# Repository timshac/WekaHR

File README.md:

# WekaHR modbus slave holding registers synchronised with google sheets

The WekaHR is a modbus slave (RS-485) with read/write registers that are synced with your google sheet. Your PLC can connect to the WekaHR modbus slave to read and write register values to report data or configure PLC operations.

## Components

* WekaHR featherwing
* a PLC (supplied by you)
* Particle Argon (Wifi) or Boron (cellular) IOT device
* Google Sheet Application

## Connect hardware

1. Wire the WekaHR to your PLC.  The WekaHR is powered by 5v DC. Schnieder PLCs provide 5v via the modbus port
2. Insert the Boron or Argon into the WekaHR
3. Connnect particle Boron or Argon to the particle cloud, and give the device a name (deviceName)

Then you are ready to flash the firmware

## Flash Firmware

Clone this repository, and install the [particle command line tools](https://docs.particle.io/tutorials/developer-tools/cli/)

```
cd WekaHR/firmware/particle_gen3
# compile and flash over WiFi or Cellular
particle flash deviceName 

# or, for usb connected particle
particle compile argon|boron --saveTo=bin
particle serial list
particle serial flash bin
```

## Initial WekaHR module setup, for a fresh new module

Issue these commands to in the particle console (console.particle.io). The modbus baud is set in the code, currently to 19200 8N1
```
SetUnitID 10   # to set modbus slave ID (defaults to 10)
SetEventName "companyname/projectname"   # set the particle webhook event name

```

## Save a copy of the linked google sheet

Save a copy of this [WekaHR Google Sheets Template](https://docs.google.com/spreadsheets/d/1dsoAosavrSCt88q0tjWTA6WfT7lwxBgexuUGqGGjWAQ/copy?usp=sharing) and follow the instructions in the worksheet to connect your particle to the google sheet using a webhook.

## Connect particle cloud to google sheet

Follow the instructions in the google sheet to connect your particle device to the google sheeet using a particle webhook integration.

## Particle API - Functions

#### int ManualUpdate(String args = "")

Trigger a manual JSON packet publish and JSON settings register response.  Running this function ensures that application register values are set in the WekaHR.

#### int PublishUnitID(String args = "")

Publish the current modbus id. Defaults to 10.

#### int SetUnitID(String args = "number 1-247")

Set the device modbus id.

#### int PublishEventName(String args = "")

Publish the current event name.

#### int SetEventName(String args = "eventName")

Set the current event name.  Suggested format is CompanyName/ProjectName, where multiple customer sites may share the same CompanyName and ProjectName.

#### int PublishSettingsJSON(String args)

Publish the current JSON settings saved to EEPROM.  

#### int SetSettingsJSON(String args)

Save string args as current JSON settings to EEPROM.  Use with caution.

## JSON Published to Google Sheet

```
JSON:
{
  "name": "companyname/dairyshed",
  "data": "{\"v\":\"1.0\",\"func\":\"writeLog\",\"addr\":0,\"HR\":[0,0,0,0,0,0,0,0,0,0,0,0,0,0,0,0,0,0,2048,0,0,0,0,0,0,0,0,0,0,0,0,0,0,0,0,0,0,0,0,0,0,0,0,0,0,0,0,0,0,0,0,0,0,0,0,0,0,0,0,0,0,0,0,0,0,0,0,0,0,0,0,0,0,0,0,0,0,0,0,0]}",
  "ttl": 60,
  "published_at": "2019-10-20T01:54:46.580Z",
  "coreid": "coreid"
}

the data key, when interpreted as JSON:
{"v":"1.0","func":"writeLog","addr":0,"HR":[0,0,0,0,0,0,0,0,0,0,0,0,0,0,0,0,0,0,2048,0,0,0,0,0,0,0,0,0,0,0,0,0,0,0,0,0,0,0,0,0,0,0,0,0,0,0,0,0,0,0,0,0,0,0,0,0,0,0,0,0,0,0,0,0,0,0,0,0,0,0,0,0,0,0,0,0,0,0,0,0]}

```

Version "v" key, "v" = "1.0", where 1.0 could be anything < 2.0.  (eg 1.1,1.2, etc)
The holding registers are given as an array, starting at address "addr".
HR = [javascript array].  The current length of the array is 80 [registers addr + 0 to addr + 79], but could be anything from length 1-100.

The WekaHR accepts a JSON response that sets HR values.  The response looks like:

```

{"40":1,"41":2,"42":3,"43":0,"44":0,"45":0,"46":0,"47":0,"48":0,"49":0,"50":0,"51":0,"52":0,"53":0,"54":0,"55":0,"56":0,"57":0,"58":0,"59":0,"60":0,"61":0,"62":0,"63":0,"64":0,"65":0,"66":0,"67":0,"68":0,"69":0,"70":0,"71":0,"72":0,"73":0,"74":0,"75":0,"76":0,"77":0,"78":0,"79":12,"sheet":"https://docs.google.com/a/xxx.xxx.xxx/spreadsheets/d/yyyyyyyyyyyyyyyyyyyyyyyyyyyyyyyyyyyyyyyy/edit","row":38}

```

This includes registers set and their numeric value to be set, as well as the source google sheet or application url.

## Licenses

* Hardware: CERN-OHL-P
* Firmware: MIT
* Documentation: MIT

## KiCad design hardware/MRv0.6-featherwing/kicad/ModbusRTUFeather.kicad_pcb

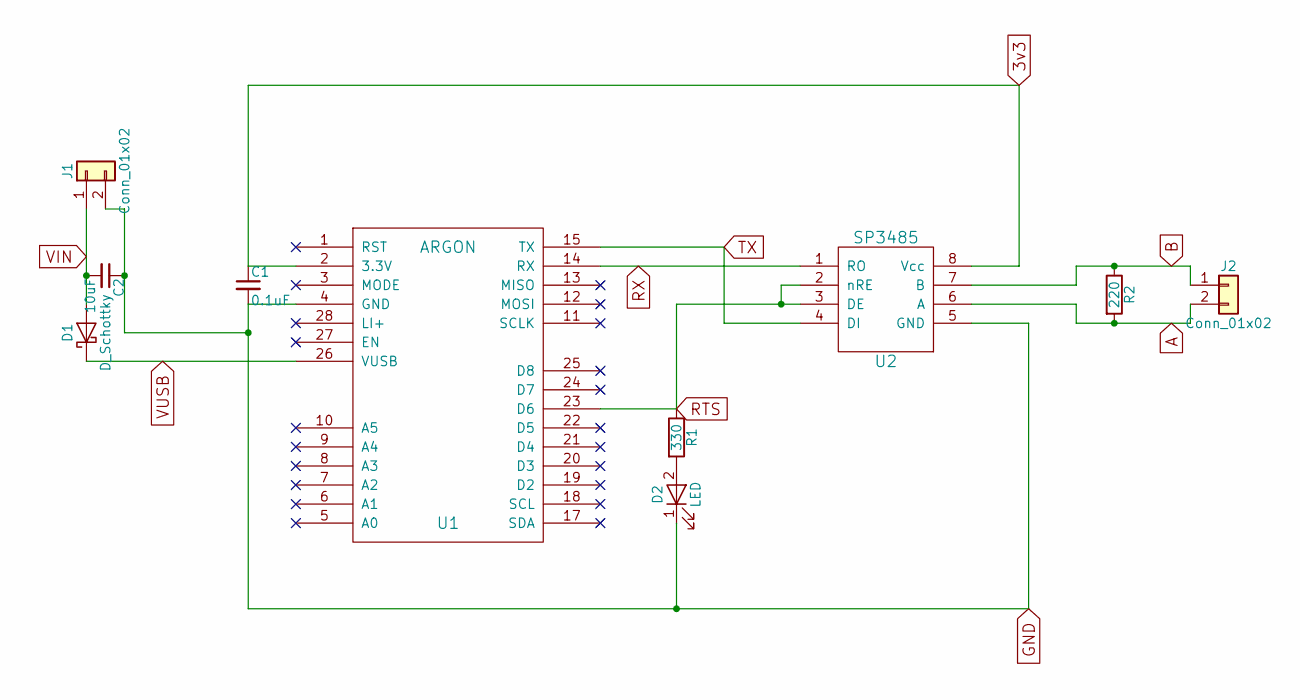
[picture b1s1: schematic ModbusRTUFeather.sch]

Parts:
C1: 0.1uF; C_0603_HandSoldering
C2: 10uF; C_0805_HandSoldering
D1: D_Schottky; D_SOD-323_HandSoldering
D2: LED; LED_0603_HandSoldering
J1, J2: Conn_01x02; TerminalBlock_Pheonix_PT-3.5mm_2pol
R1: 330; R_0603_HandSoldering
R2: 220; R_0603_HandSoldering
U1: ARGON; FeatherWing
U2: SP3485; SOIC-8_3.9x4.9mm_Pitch1.27mm

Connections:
3v3: C1.1, U1.2 (3.3V), U2.8 (Vcc)
A: J2.2, R2.2, U2.6 (A)
B: J2.1, R2.1, U2.7 (B)
GND: C1.2, C2.1, D2.1 (K), J1.2, U1.4 (GND), U2.5 (GND)
unnamed: D2.2 (A), R1.2
RTS: R1.1, U1.23 (D6), U2.2 (nRE), U2.3 (DE)
RX: U1.14 (RX), U2.1 (RO)
TX: U1.15 (TX), U2.4 (DI)
VIN: C2.2, D1.2 (A), J1.1
VUSB: D1.1 (K), U1.26 (VUSB)

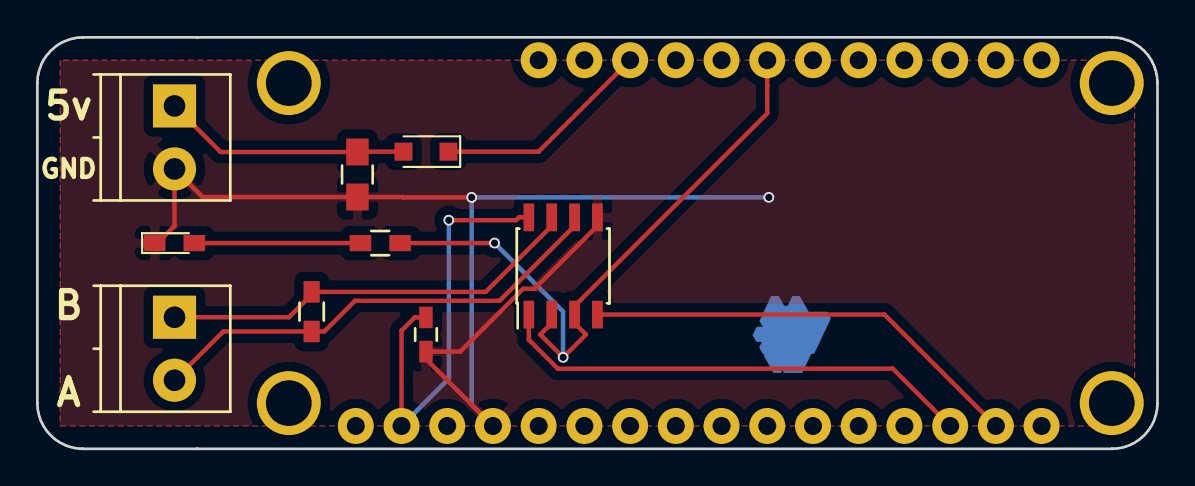
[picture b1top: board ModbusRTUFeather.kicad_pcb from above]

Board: 2 copper layers, 62.2 x 22.9 mm, 12 parts (1 on the bottom side), 10 nets.

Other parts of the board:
PCB**: VAL**; PCB_FeatherWing_4hole
SHAClogo2: G***; SHAClogo2

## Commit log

2020-06-05 initial
2020-06-05 fix numbers
2020-08-05 change to 9600 baud. Log serial out
2020-08-05 back to 19200 baud
2020-08-05 update readme to indicate baud rate
2021-04-23 update license

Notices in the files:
hardware/MRv0.6-featherwing/kicad/ModbusRTUFeather.kicad_pcb:
(c) 2019
